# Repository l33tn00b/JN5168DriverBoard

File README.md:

# JN5168DriverBoard
Companion to JN5168 Carrier Board. Provides four nMOS FETs with FET drivers for boosting control voltage.

To be used for connecting LED strips or plain voltage driven LEDs. The chosen MOSFETs are rated up to 16A and give plenty of headroom (that is just another way of saying "...and are pretty much of an overkill"). While being logic level FETs, space for FET driver ICs is provided. So one may choose another FET (non-logic-level) in conjunction with the driver ICs. Or omit the driver ICs and go for the logic level FET. If you go towards the maximum rating of the FETs you might consider mounting the entire board on something suitable for heat dissipation. Normal operation at 20W per channel is not not much of a problem.

# Board Pictures (Prototypes)

.JPG)

.JPG)

Prototype boards shown here made by www.aisler.net (not affiliated in any way).

# Load Testing 

Load testing was performed using 10W resistors:

# See also:

http://www.boriswerner.eu/tinkering-tuesday-hueify-pwm-to-rgb-led-strip-driver-board

https://peeveeone.com/?page_id=252

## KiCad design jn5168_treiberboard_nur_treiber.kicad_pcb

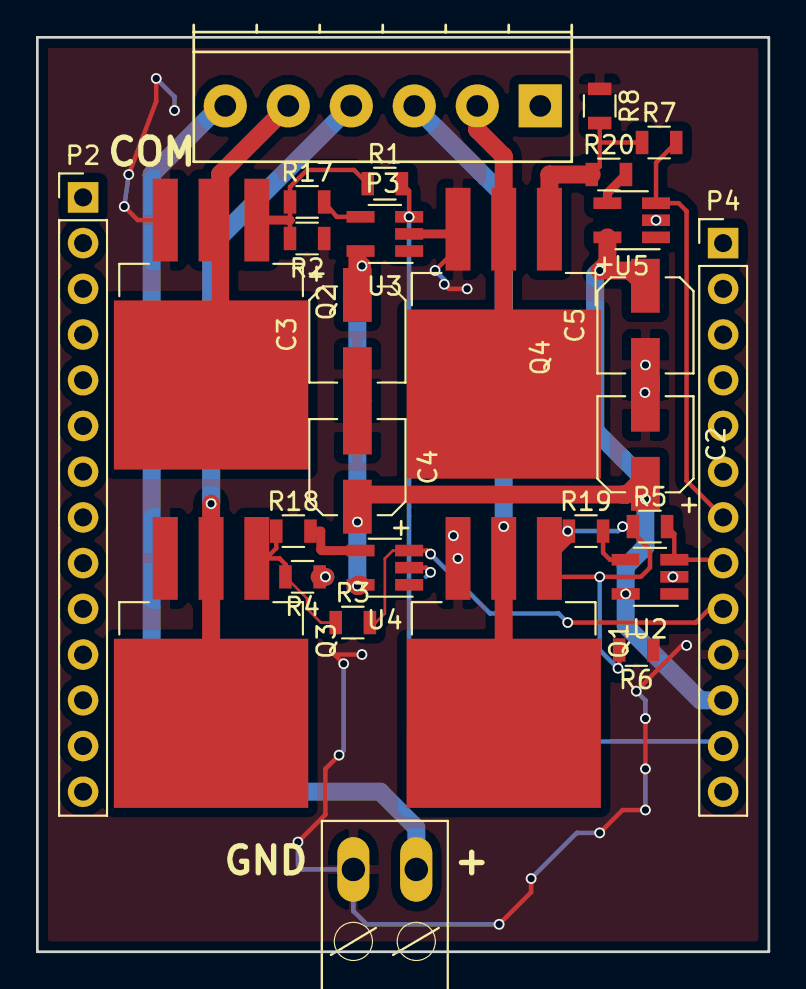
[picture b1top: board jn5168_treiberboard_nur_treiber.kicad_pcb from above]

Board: 2 copper layers, 40.6 x 50.8 mm, 28 parts (0 on the bottom side), 19 nets.

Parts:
C2, C3, C4, C5: 10uF; CP_Elec_5x5.8
CONN1: RIACON-2; con-riacon-RIACON-2
P2: CONN_01X14; Pin_Header_Straight_1x14_Pitch2.54mm
P3: CONN_01X06; TerminalBlock_Pheonix_PT-3.5mm_6pol
P4: CONN_01X13; Pin_Header_Straight_1x13_Pitch2.54mm
Q1, Q2, Q3, Q4: STB16NF06LT4; TO-263-3Lead
R1, R3, R5, R7: 0R; R_0805
R2, R4, R6, R8: 10k; R_0805
R17, R18, R19, R20: 1k; R_0805
U2, U3, U4, U5: LTC1981; SOT-23-5_HandSoldering

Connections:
+3V3: C2.1, C3.1, C4.1, C5.1, P4.11, U2.5, U3.5, U4.5, U5.5
/Conn_B: P3.3, Q1.2
/Conn_G: P3.4, Q3.2
/Conn_R: P3.5, Q2.2
/Conn_W: P3.2, Q4.2
/PWM0: P4.12, R1.2, U3.3
/PWM1: P4.9, R3.2, U4.3
/PWM2: P4.8, R5.2, U2.3
/PWM3: P4.7, R7.2, U5.3
GND: C2.2, C3.2, C4.2, C5.2, CONN1.P$1, P4.10, Q1.3, Q2.3, Q3.3, Q4.3, R2.1, R4.1, R6.1, R8.1, U2.2, U3.2, U4.2, U5.2
unnamed: CONN1.P$2, P3.6
unnamed: Q1.1, R5.1, R6.2, R19.1
unnamed: Q2.1, R1.1, R2.2, R17.1
unnamed: Q3.1, R3.1, R4.2, R18.1
unnamed: Q4.1, R7.1, R8.2, R20.1
unnamed: R17.2, U3.4
unnamed: R18.2, U4.4
unnamed: R19.2, U2.4
unnamed: R20.2, U5.4

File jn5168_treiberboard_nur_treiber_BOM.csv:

Reference;Value;Footprint;Count;Datasheet;FootprintLib
CONN1;RIACON-2;con-riacon-RIACON-2;1;;riacon2_dixed
Q1,Q2,Q3,Q4;STB16NF06LT4;TO-263-3Lead;4;;TO_SOT_Packages_SMD
U2,U3,U4,U5;LTC1981;SOT-23-5_HandSoldering;4;;TO_SOT_Packages_SMD
C4,C2,C3,C5;10uF;CP_Elec_5x5.8;4;;Capacitors_SMD
R19,R17,R18,R20;1k;R_0805;4;;Resistors_SMD
P2;CONN_01X14;Pin_Header_Straight_1x14_Pitch2.54mm;1;;Pin_Headers
P4;CONN_01X13;Pin_Header_Straight_1x13_Pitch2.54mm;1;;Pin_Headers
P3;CONN_01X06;TerminalBlock_Pheonix_PT-3.5mm_6pol;1;;Terminal_Blocks
R2,R4,R6,R8;10k;R_0805;4;;Resistors_SMD
R1,R3,R5,R7;0R;R_0805;4;;Resistors_SMD

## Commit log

2017-05-23 Add files via upload
    PDF of schematic uploaded.
2017-05-25 Add files via upload
    BOM as HTML file
2017-05-25 Add files via upload
    BOM as euro-style .csv file.
2017-05-25 Add files via upload
    BOM as HTML file.
2017-05-25 Add files via upload
    Picture of PCB (no components placed).
2017-05-25 Add files via upload
    Picture of PCB. Components for one driver stage (plus an additional capacitor) have been placed. (Capacitors are SMD on through-hole places, bad hack ;) )
2017-05-25 Update README.md
    Insert link to Boris' site.
2017-05-25 Update README.md
    added link to Peter's site.
2017-05-26 Add files via upload
    Picture of load testing setup.
